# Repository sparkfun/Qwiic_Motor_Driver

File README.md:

SparkFun Qwiic_Motor_Driver
========================================

[*SparkFun Qwiic Motor Driver (15451)*](https://www.sparkfun.com/products/15451)

The SparkFun Qwiic Motor Driver takes all the great features of the Serial Controlled Motor Driver (SCMD) and miniaturizes them, adding [Qwiic](https://www.sparkfun.com/qwiic) ports for plug and play functionality. Boasting the same 4245 PSOC and 2-channel motor ports as the SCMD, the SparkFun Qwiic Motor Driver is designed to communicate over I<sup>2</sup>C to make setting up your next robotic project as fast and easy as possible! Utilizing our handy Qwiic system, no soldering is required to connect it to the rest of your system. 

With 1.2A steady state drive per channel (1.5A peak) and 127 levels of DC drive strength, this little Qwiic board is perfect for your small DC motor driver needs. Since the Qwiic Motor Driver is a 3.3V logic device, you'll need to use a logic level converter to interface to 5V.

Repository Contents
-------------------

* **/Hardware** - Eagle design files (.brd, .sch)

Documentation
--------------
* **[Serial Controlled Motor Driver Library](https://github.com/sparkfun/SparkFun_Serial_Controlled_Motor_Driver_Arduino_Library)** - Arduino library for the Qwiic Motor Driver.
* **[Hookup Guide](https://learn.sparkfun.com/tutorials/hookup-guide-for-the-qwiic-motor-driver)** - Basic hookup guide for the Qwiic Motor Driver.

License Information
-------------------

This product is _**open source**_! 

Please review the LICENSE.md file for license information. 

If you have any questions or concerns on licensing, please contact technical support on our [SparkFun forums](https://forum.sparkfun.com/viewforum.php?f=152).

Distributed as-is; no warranty is given.

- Your friends at SparkFun.

_<COLLABORATION CREDIT>_

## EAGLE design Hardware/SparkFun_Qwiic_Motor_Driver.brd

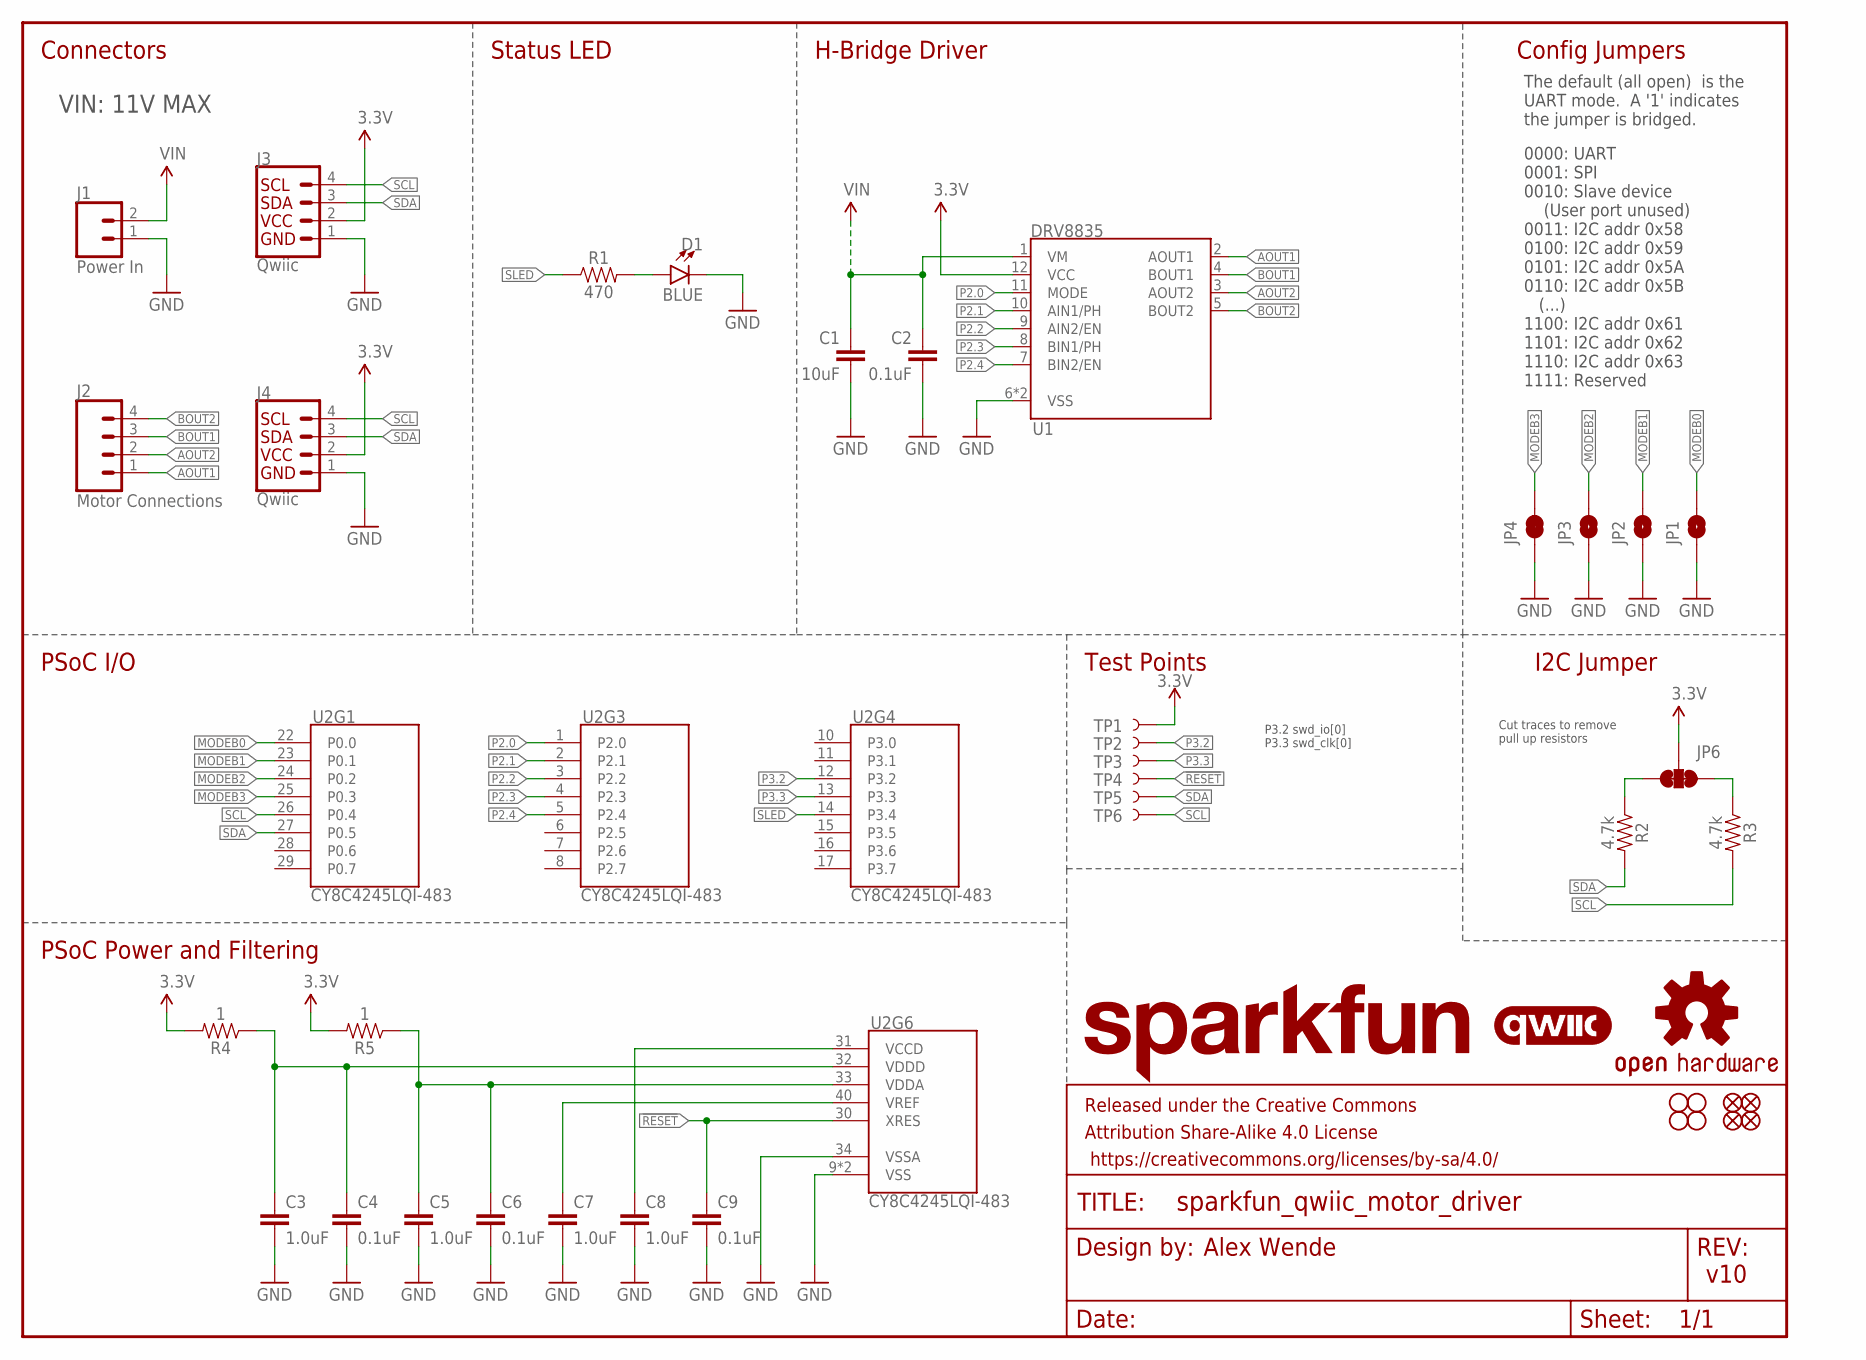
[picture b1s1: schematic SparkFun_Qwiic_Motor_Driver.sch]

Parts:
C1: 10uF; 0805
C2, C4, C6, C9: 0.1uF; 0402
C3, C5, C7, C8: 1.0uF; 0402
D1: BLUE; LED-0603
FD1, FD2, FD3, FD4: FIDUCIALUFIDUCIAL; FIDUCIAL-MICRO
FRAME1: FRAME-LETTER; CREATIVE_COMMONS
H1, H2, H3, H4: STAND-OFF
J1: Power In; SCREWTERMINAL-3.5MM-2
J2: Motor Connections; SCREWTERMINAL-3.5MM-4
J3, J4: Qwiic; JST04_1MM_RA
JP1, JP2, JP3: JUMPER-PAD-2; SMT-JUMPER_2_NO_NO-SILK
JP4: JUMPER-PAD-2; SMT-JUMPER_2_NC_TRACE_NO-SILK
JP6: JUMPER-SMT_3_2-NC_TRACE_NO-SILK; SMT-JUMPER_3_2-NC_TRACE_NO-SILK
LOGO2: OSHW-LOGOMINI; OSHW-LOGO-MINI
LOGO3: SFE_LOGO_NAME.1_INCH; SFE_LOGO_NAME_.1
R1: 470; 0603
R2, R3: 4.7k; 0603
R4, R5: 1; 0603
TP1, TP2, TP3, TP4, TP5, TP6: TEST-POINTTP_15TH_THRU; TP_15TH
U1: DRV8835; WSON-12
U2: CY8C4245LQI-483; QFN-40
U$1: QWIIC_LOGO_5MM; QWIIC_5MM

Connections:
3.3V: J3.2, J4.2, JP6.2, R4.2, R5.2, TP1.P$1, U1.12 (VCC)
!RESET: C9.1, TP4.P$1, U2.30 (XRES)
AOUT1: J2.1, U1.2 (AOUT1)
AOUT2: J2.2, U1.3 (AOUT2)
BOUT1: J2.3, U1.4 (BOUT1)
BOUT2: J2.4, U1.5 (BOUT2)
GND: C1.2, C2.2, C3.2, C4.2, C5.2, C6.2, C7.2, C8.2, C9.2, D1.C, J1.1, J3.1, J4.1, JP1.1, JP2.1, JP3.1, JP4.1, U1.6 (VSS), U1.PAD (VSS), U2.9 (VSS), U2.34 (VSSA), U2.EP (VSS)
MODEB0: JP1.2, U2.22 (P0.0)
MODEB1: JP2.2, U2.23 (P0.1)
MODEB2: JP3.2, U2.24 (P0.2)
MODEB3: JP4.2, U2.25 (P0.3)
unnamed: C8.1, U2.31 (VCCD)
unnamed: C5.1, C6.1, R5.1, U2.33 (VDDA)
unnamed: C7.1, U2.40 (VREF)
unnamed: D1.A, R1.2
unnamed: JP6.1, R3.1
unnamed: JP6.3, R2.1
P2.0: U1.11 (MODE), U2.1 (P2.0)
P2.1: U1.10 (AIN1/PH), U2.2 (P2.1)
P2.2: U1.9 (AIN2/EN), U2.3 (P2.2)
P2.3: U1.8 (BIN1/PH), U2.4 (P2.3)
P2.4: U1.7 (BIN2/EN), U2.5 (P2.4)
P3.2: TP2.P$1, U2.12 (P3.2)
P3.3: TP3.P$1, U2.13 (P3.3)
SCL: J3.4, J4.4, R3.2, TP6.P$1, U2.26 (P0.4)
SDA: J3.3, J4.3, R2.2, TP5.P$1, U2.27 (P0.5)
SLED: R1.1, U2.14 (P3.4)
VDDD: C3.1, C4.1, R4.1, U2.32 (VDDD)
VIN: C1.1, C2.1, J1.2, U1.1 (VM)

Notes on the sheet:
PSoC Power and Filtering
Config Jumpers
Alex Wende
PSoC I/O
v10
P3.2 swd_io[0] P3.3 swd_clk[0]
0000: UART 0001: SPI 0010: Slave device (User port unused) 0011: I2C addr 0x58 0100: I2C addr 0x59 0101: I2C addr 0x5A 0110: I2C addr 0x5B (...) 1100: I2C addr 0x61 1101: I2C addr 0x62 1110: I2C addr 0x63 1111: Reserved
The default (all open) is the UART mode. A '1' indicates the jumper is bridged.
Connectors
Status LED
H-Bridge Driver
Test Points
I2C Jumper
VIN: 11V MAX
Cut traces to remove pull up resistors

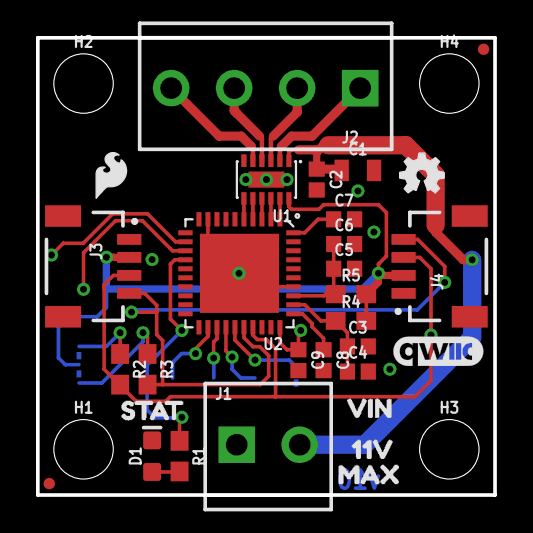
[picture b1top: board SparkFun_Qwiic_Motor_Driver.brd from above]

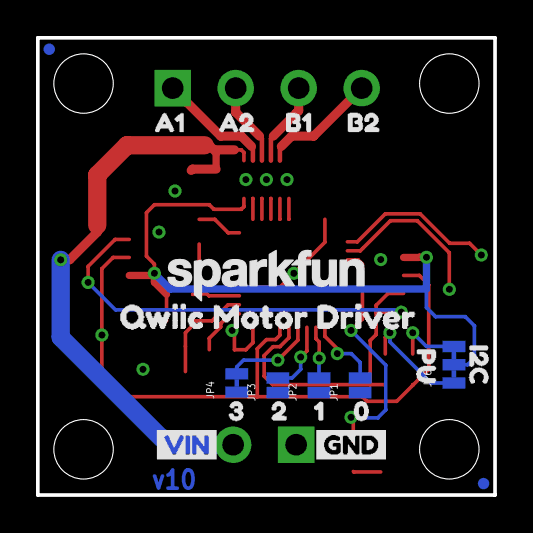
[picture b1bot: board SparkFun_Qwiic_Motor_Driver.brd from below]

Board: 2 copper layers, 25.4 x 25.4 mm, 62 parts (21 on the bottom side), 29 nets.

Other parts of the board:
U$2: STAT4
U$3: GND3
U$4: VIN2
U$5: 05
U$6: 16
U$7: 27
U$8: 38
U$9: A110
U$10: A211
U$11: B112
U$12: B213
U$13: 11V7
U$14: MAX8
U$15: VIN6
U$16: I2C0
U$17: PU1
U$18: QWIIC_MOTOR_DRIVER0
U$19: SFE_LOGO_FLAME_.1

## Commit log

2019-06-26 v01 Design Review Changes
    - Added I2C test points
    - Moved motor connector symbol to connection section
    - Changed status LED to blue
    - Adjusted VIN trace width
    - Added SFE flame to top side of board
2019-07-22 v10 Update
    - Added new 4-pin screw terminal instead of 2x2-pin screw terminals
    - Added note about cutting traces to disable I2C pullup resistors
2019-07-23 v10 QC changes
    Updated PROD_ID for the 4-pin screw terminal
2019-09-03 Update SparkFun_Qwiic_Motor_Driver.sch
    Updated the config jumpers section of the schematic of valid addresses

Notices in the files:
parts and their libraries:
SparkFun-Capacitors: Licensing: Creative Commons ShareAlike 4.0 International - https://creativecommons.org/licenses/by-sa/4.0
SparkFun-Aesthetics: Released under the Creative Commons Attribution Share-Alike 4.0 License
SparkFun-Aesthetics: https://creativecommons.org/licenses/by-sa/4.0
